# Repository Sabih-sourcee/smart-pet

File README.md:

## I Made An Robot That Can Help You Learn Computer

- Smart-Pet is a robot that can watch your screen that what you are doing and can guide you about whatever you are learing is in the right wau you are learning or not

## Smartpet Server

- This branch was all about code i have written for making it in real life like how is there server is going to be running
- How the code behind works
- How robot able to see your screen
- How it can guide you after it

## PCB

- This brnach contains all the Kicad files i have made.
- It has pcb, sch, gerbers and others which i am going to make.

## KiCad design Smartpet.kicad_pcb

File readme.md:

## We are making Assistant for Computer begineers

- What we are making is a Robot which can always view your screen and according to that guide you for completing tasks as per if someone is new in using computer it can help them.

- Its not a simple chatbot because you dont have to everytime explain from start that what i am doing or what i have done but everytime when u screen changes it automatically detects that and identify that whats changed and is this change is a way to stucking more or is it a acheivement for such task

- It can help those corporate oldies or too beginner ages from 11-15 aged kids to learn computer using it.

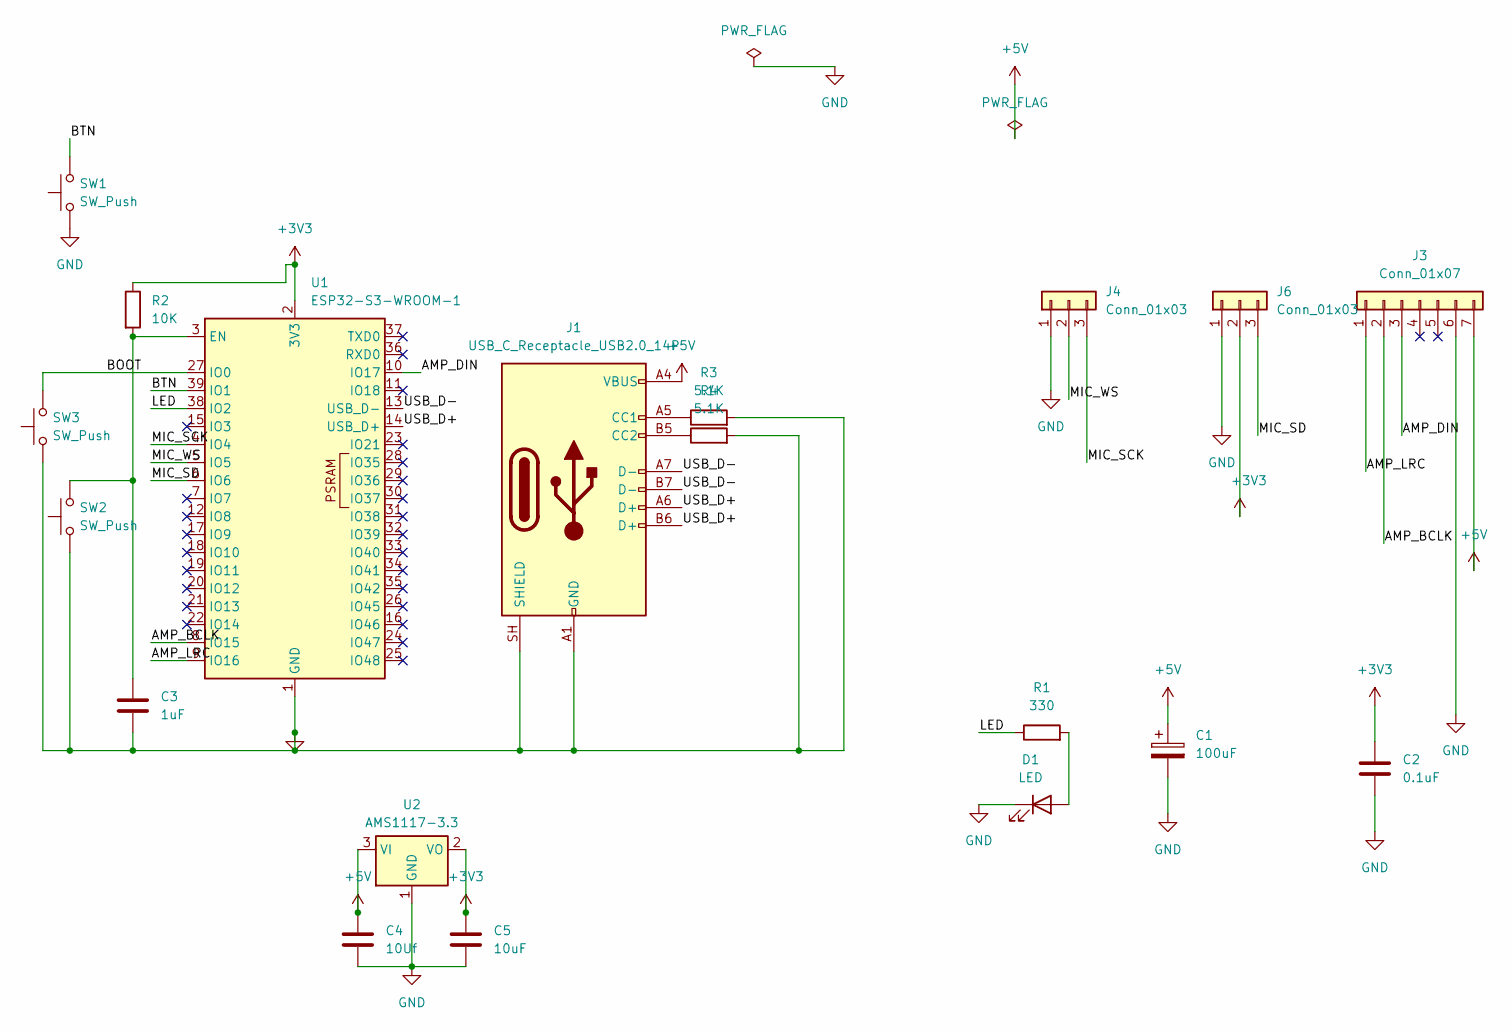
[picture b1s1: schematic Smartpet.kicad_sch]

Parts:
C1: 100uF; CP_Radial_D6.3mm_P2.50mm
C2: 0.1uF; C_Disc_D5.0mm_W2.5mm_P5.00mm
C3: 1uF; C_Disc_D5.0mm_W2.5mm_P5.00mm
C4: 10Uf; C_Disc_D5.0mm_W2.5mm_P5.00mm
C5: 10uF; C_Disc_D5.0mm_W2.5mm_P5.00mm
D1: LED; LED_D5.0mm
J1: USB_C_Receptacle_USB2.0_14P; USB_C_Receptacle_GCT_USB4105-xx-A_16P_TopMnt_Horizontal
J3: Conn_01x07; PinSocket_1x07_P2.54mm_Vertical
J4, J6: Conn_01x03; PinSocket_1x03_P2.54mm_Vertical
R1: 330; R_Axial_DIN0207_L6.3mm_D2.5mm_P7.62mm_Horizontal
R2: 10K; R_Axial_DIN0207_L6.3mm_D2.5mm_P7.62mm_Horizontal
R3, R4: 5.1K; R_Axial_DIN0207_L6.3mm_D2.5mm_P7.62mm_Horizontal
SW1, SW2, SW3: SW_Push; SW_PUSH_6mm
U1: ESP32-S3-WROOM-1
U2: AMS1117-3.3; SOT-223-3_TabPin2

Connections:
+3V3: C2.1, C5.1, J6.2, R2.1, U1.2 (3V3), U2.2 (VO)
+5V: C1.1, C4.1, J1.A4 (VBUS), J1.A9 (VBUS), J1.B4 (VBUS), J1.B9 (VBUS), J3.7, U2.3 (VI)
/AMP_BCLK: J3.2, U1.8 (IO15)
/AMP_DIN: J3.3, U1.10 (IO17)
/AMP_LRC: J3.1, U1.9 (IO16)
/BOOT: SW3.2, U1.27 (IO0)
/BTN: SW1.2, U1.39 (IO1)
/LED: R1.1, U1.38 (IO2)
/MIC_SCK: J4.3, U1.4 (IO4)
/MIC_SD: J6.3, U1.6 (IO6)
/MIC_WS: J4.2, U1.5 (IO5)
/USB_D+: J1.A6 (D+), J1.B6 (D+), U1.14 (USB_D+)
/USB_D-: J1.A7 (D-), J1.B7 (D-), U1.13 (USB_D-)
GND: C1.2, C2.2, C3.2, C4.2, C5.2, D1.1 (K), J1.A1 (GND), J1.A12 (GND), J1.B1 (GND), J1.B12 (GND), J1.SH (SHIELD), J3.6, J4.1, J6.1, R3.2, R4.2, SW1.1, SW2.1, SW3.1, U1.1 (GND), U1.40 (GND), U1.41 (GND), U2.1 (GND)
unnamed: D1.2 (A), R1.2
unnamed: J1.A5 (CC1), R3.1
unnamed: J1.B5 (CC2), R4.1
unnamed: C3.1, R2.2, SW2.2, U1.3 (EN)

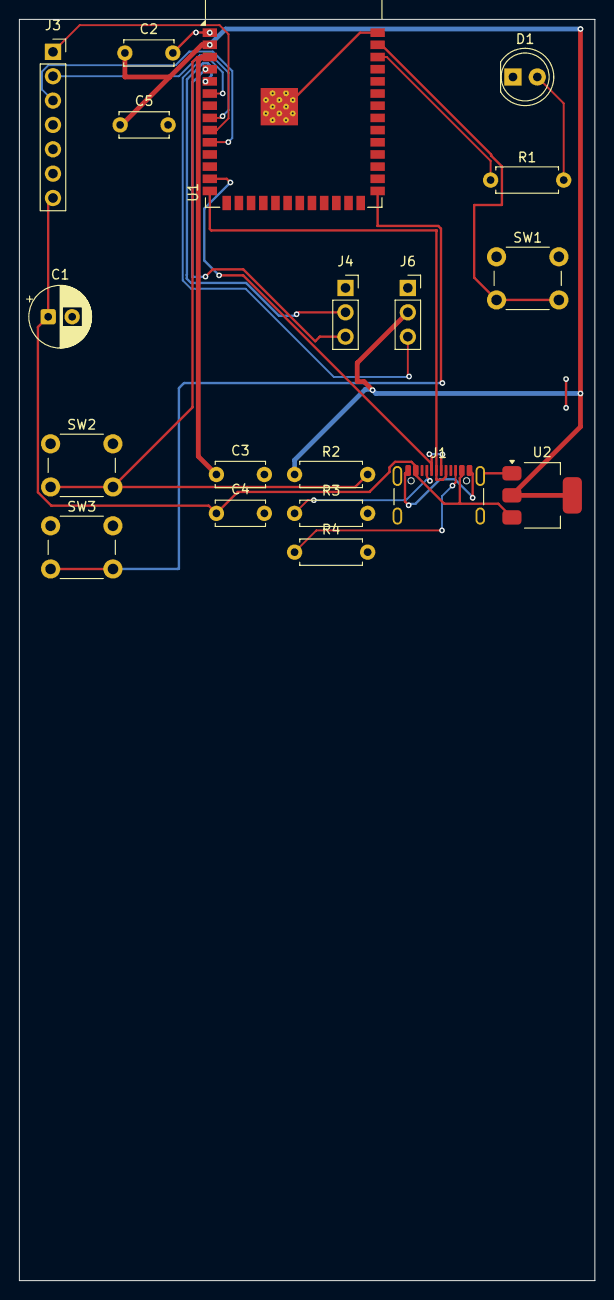
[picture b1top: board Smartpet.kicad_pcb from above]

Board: 2 copper layers, 60.0 x 131.5 mm, 19 parts (0 on the bottom side), 18 nets.
